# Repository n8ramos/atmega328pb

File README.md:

# design assignments with AVR
CPE301 design assignments on the atmega328pb micro-processor

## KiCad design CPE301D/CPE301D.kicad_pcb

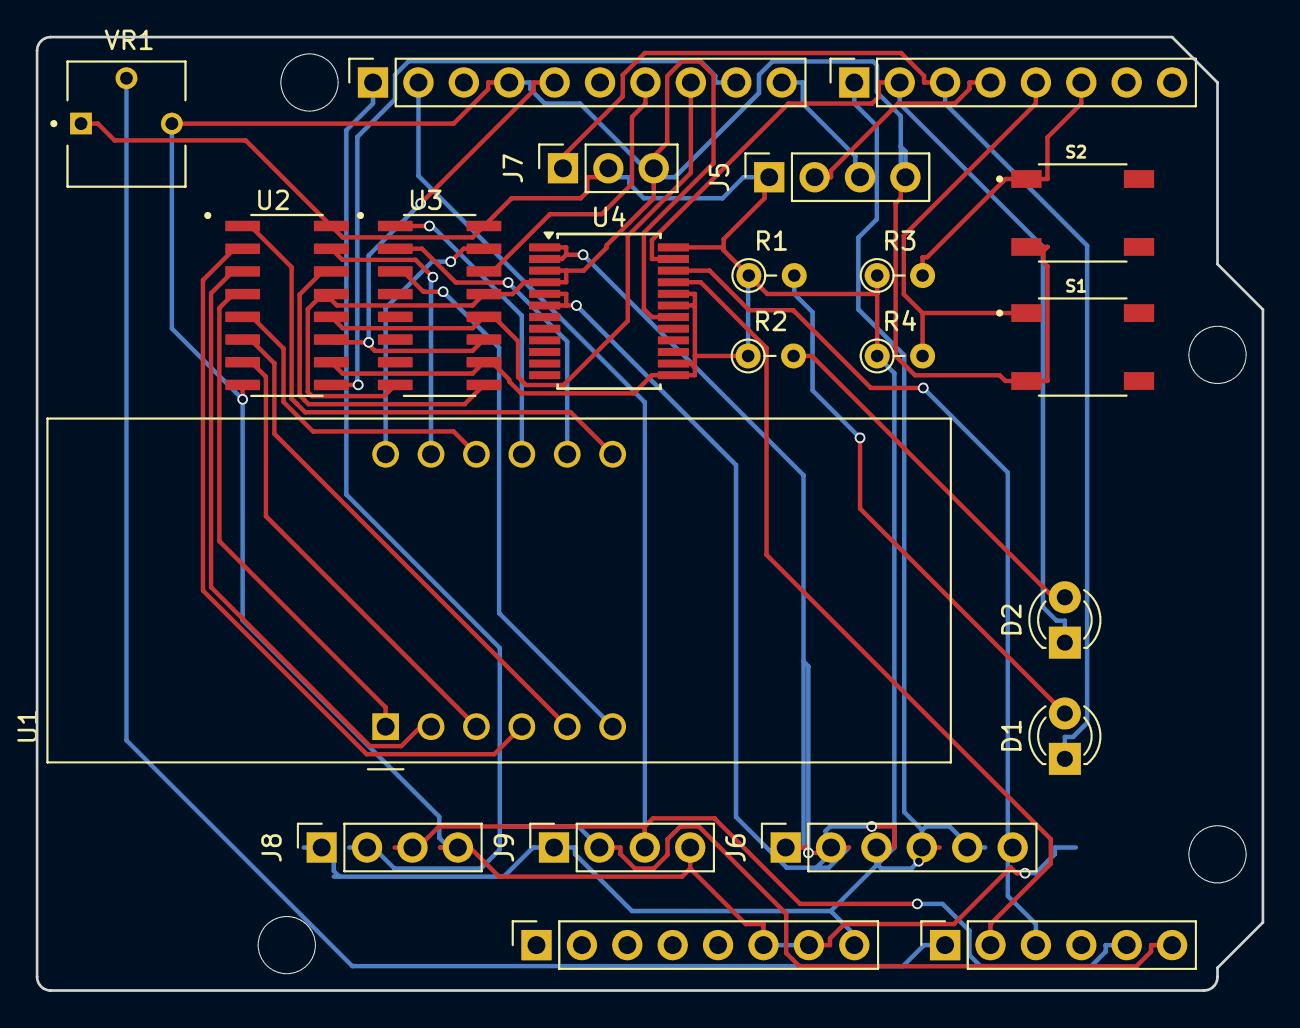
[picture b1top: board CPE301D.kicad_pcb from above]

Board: 2 copper layers, 68.6 x 53.3 mm, 26 parts (0 on the bottom side), 35 nets.

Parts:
D1, D2: LED; LED_D3.0mm
J1: Power; PinSocket_1x08_P2.54mm_Vertical
J2: Digital/PWM; PinSocket_1x10_P2.54mm_Vertical
J3: Analog; PinSocket_1x06_P2.54mm_Vertical
J4: Digital/PWM; PinSocket_1x08_P2.54mm_Vertical
J5: HC-SR04 Connectors; PinSocket_1x04_P2.54mm_Vertical
J6: PPTC061LFBN-RC; PinSocket_1x06_P2.54mm_Vertical
J7: Servo Connectors; PinSocket_1x03_P2.54mm_Vertical
J8, J9: I2C Connectors; PinSocket_1x04_P2.54mm_Vertical
MH1, MH2, MH3, MH4: MountingHole_3.2mm
R1, R2: 510; R_Axial_DIN0204_L3.6mm_D1.6mm_P2.54mm_Vertical
R3, R4: 10k; R_Axial_DIN0204_L3.6mm_D1.6mm_P2.54mm_Vertical
S1, S2: 8-1437565-1; SW_8-1437565-1
U1: CC56-12SRWA; CA56-12SRWA
U2, U3: MC74HC595AD; SOIC127P600X175-16N
U4: TB6612FNG; SSOP-24_5.3x8.2mm_P0.65mm
VR1: 3362P-1-103LF; TRIM_3362P-1-103LF

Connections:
/2: J4.6, R3.2, S2.1
/4: J4.4, J5.2
/7: J4.1, J6.4
/8: J2.10, J5.3
/13: J2.5, U2.11 (SHIFT_CLK), U3.11 (SHIFT_CLK)
/*3: J4.5, R4.2, S1.1
/*5: D1.1 (K), J4.3, J7.1
/*6: D2.1 (K), J4.2, U4.23 (PWMA)
/*9: J2.9, U2.9 (SQH)
/*10: J2.8, U2.12 (LATCH_CLK), U3.12 (LATCH_CLK)
/*11: J2.7, U3.14 (A)
/A0: J3.1, VR1.2
/A1: J3.2, U4.21 (AIN1)
/A2: J3.3, U4.22 (AIN2)
/CC1: U1.12 (CC1), U3.15 (QA)
/SCL/A5: J2.1, J3.6, J8.2, J9.2
/SDA/A4: J2.2, J3.5, J8.3, J9.3
/SQH to A: U2.14 (A), U3.9 (SQH)
/a: U1.11 (a), U2.15 (QA)
GND: J1.6, J1.7, J2.4, J5.4, J6.6, J7.3, J8.4, J9.4, S1.3, S2.3, U2.8 (GND), U2.13 (OE), U3.8 (GND), U3.13 (OE), U4.3 (PGND1), U4.4 (PGND1), U4.18 (GND), VR1.3
unnamed: D1.2 (A), R1.2
unnamed: D2.2 (A), R2.2
unnamed: J6.1, U4.1 (AO1), U4.2 (AO1)
unnamed: J6.2, U4.5 (AO2), U4.6 (AO2)
unnamed: U1.9 (CC2), U3.1 (QB)
unnamed: U1.8 (CC3), U3.2 (QC)
unnamed: U1.6 (CC4), U3.3 (QD)
unnamed: U1.3 (DPX), U2.7 (QH)
unnamed: U1.7 (b), U2.1 (QB)
unnamed: U1.4 (c), U2.2 (QC)
unnamed: U1.2 (d), U2.3 (QD)
unnamed: U1.1 (e), U2.4 (QE)
unnamed: U1.10 (f), U2.5 (QF)
unnamed: U1.5 (g), U2.6 (QG)
VCC: J1.8, J5.1, J6.3, J7.2, J8.1, J9.1, R1.1, R2.1, R3.1, R4.1, U2.10 (RESET), U2.16 (VCC), U3.10 (RESET), U3.16 (VCC), U4.13 (VM2), U4.14 (VM3), U4.19 (STBY), U4.20 (VCC), U4.24 (VM1), VR1.1

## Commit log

2024-03-08 Design Assignment 2
2024-04-15 Add files via upload
    design assignment 4
2024-04-22 Design Assignment 5
2024-05-07 Design Assignment 6
2024-05-09 KICAD DA
